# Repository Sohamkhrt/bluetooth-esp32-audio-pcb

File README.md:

# bluetooth-esp32-audio-pcb
A custom Bluetooth Audio PCB for motorcycle helmets, powered by ESP32 and PCM5102A with integrated LiPo BMS and power management

Project Highlights

Core Logic: ESP32-WROOM-32 for Bluetooth A2DP audio streaming.

Audio: High-fidelity I2S interface using the PCM5102A DAC (32-bit/384kHz capable).

Power Management: Integrated TP4056 LiPo charger with DW01A protection circuitry (Over-charge/Over-discharge/Short-circuit protection).

Regulation: Low-dropout (LDO) 3.3V regulation (AP2112K) with stable capacitor banking for RF noise suppression.

Technical Challenges Solved

MOSFET Matching: Resolved a critical pinout mismatch between standard TSSOP-8 and SOT-23-6 dual N-channel MOSFETs for battery protection.

Signal Integrity: Implemented dedicated ground planes (copper pours) on both layers with stitching vias to minimize EMI and ground loops for clear audio.

Space Constraint: Designed within a tight 50mm x 50mm form factor to fit inside a helmet cheek pad.

EDA Tool Used: KiCad 9.0

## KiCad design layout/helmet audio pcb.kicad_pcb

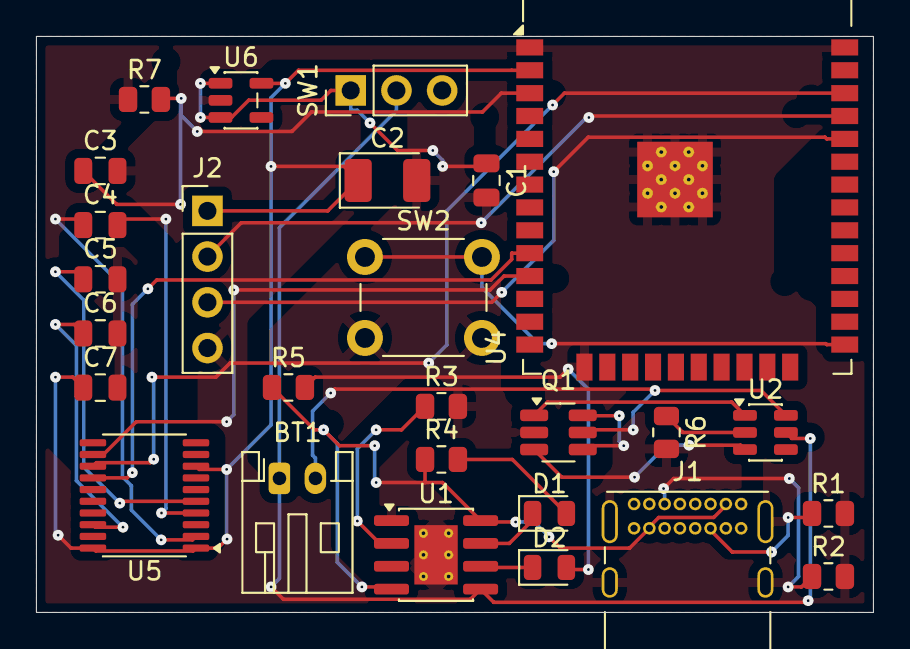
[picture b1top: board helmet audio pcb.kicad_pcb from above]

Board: 2 copper layers, 46.5 x 32.0 mm, 27 parts (0 on the bottom side), 28 nets.

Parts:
BT1: Battery_Cell; JST_PH_S2B-PH-K_1x02_P2.00mm_Horizontal
C1: 10uF; C_0805_2012Metric
C2: 100uF; CP_EIA-3528-21_Kemet-B_HandSolder
C3: 1uF; C_0805_2012Metric
C4, C5, C6: 2.2uF; C_0805_2012Metric
C7: 0.1uF; C_0805_2012Metric
D1, D2: LED; LED_0805_2012Metric
J1: USB_C_Receptacle_PowerOnly_6P; USB_C_Receptacle_GCT_USB4085
J2: Conn_01x04; PinHeader_1x04_P2.54mm_Vertical
Q1: Q_Dual_NMOS_G1S2G2D2S1D1; SOT-23-6_Handsoldering
R1, R2: 5.1k; R_0805_2012Metric
R3: 1.2k; R_0805_2012Metric
R4, R5: 1k; R_0805_2012Metric
R6: 1K; R_0805_2012Metric
R7: 10K; R_0805_2012Metric
SW1: SW_SPDT; PinHeader_1x03_P2.54mm_Vertical
SW2: SW_Push; SW_PUSH_6mm
U1: TP4056-42-ESOP8; SOIC-8-1EP_3.9x4.9mm_P1.27mm_EP2.41x3.3mm_ThermalVias
U2: DW01A; SOT-23-6
U4: ESP32-WROOM-32
U5: PCM5102A; TSSOP-20_4.4x6.5mm_P0.65mm
U6: AP2112K-3.3; SOT-23-5

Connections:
/3V3: C2.1, C7.1, J2.1, U4.2 (VDD), U5.1 (CPVDD), U5.8 (AVDD), U5.20 (DVDD), U6.5 (VOUT)
/BAT_MINUS: BT1.2 (-), Q1.5 (S), U2.6 (GND)
/BAT_RAW: BT1.1 (+), SW1.2 (B), U1.5 (BAT), U2.5 (VCC)
/GND: C1.2, C2.2, C3.2, C5.2, C6.2, C7.2, J1.A12 (GND), J1.B12 (GND), J1.S1 (SHIELD), J2.4, Q1.2 (S), R1.2, R2.2, R3.2, R6.2, R7.1, SW2.2, U1.1 (TEMP), U1.3 (GND), U1.9 (EPAD), U4.1 (GND), U4.15 (GND), U4.38 (GND), U4.39 (GND), U6.2 (GND)
/OVER_CHARGE: Q1.3 (G), U2.3 (OC)
/OVER_DISCHARGE: Q1.1 (G), U2.1 (OD)
/RXD: J2.3, U4.34 (RXD0/IO3)
/TXD: J2.2, U4.35 (TXD0/IO1)
/VBUS_IN: J1.A9 (VBUS), J1.B9 (VBUS), R4.1, R5.1, U1.4 (V_{CC}), U1.8 (CE)
/V_SYS: C1.1, SW1.1 (A), U6.1 (VIN), U6.3 (EN)
unnamed: D1.2 (A), R4.2
unnamed: D1.1 (K), U1.7 (~CHRG)
unnamed: D2.2 (A), R5.2
unnamed: D2.1 (K), U1.6 (~STDBY)
unnamed: J1.A5 (CC1), R2.1
unnamed: J1.B5 (CC2), R1.1
unnamed: Q1.4 (D), Q1.6 (D)
unnamed: R3.1, U1.2 (PROG)
unnamed: R6.1, U2.2 (CS)
unnamed: C3.1, R7.2, U4.3 (EN)
unnamed: SW2.1, U4.25 (IO0)
unnamed: U4.36 (IO22), U5.13 (BCK)
unnamed: U4.10 (IO25), U5.14 (DIN)
unnamed: U4.11 (IO26), U5.12 (SCK)
unnamed: C4.2, U5.4 (CAPM)
unnamed: C4.1, U5.2 (CAPP)
unnamed: C6.1, U5.18 (LDOO)
unnamed: C5.1, U5.5 (VNEG)

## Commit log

2026-01-20 Create schematics
2026-01-20 added schematic files
2026-01-20 Enhance README with project details and challenges
    Added project highlights, technical challenges, and EDA tool used.
